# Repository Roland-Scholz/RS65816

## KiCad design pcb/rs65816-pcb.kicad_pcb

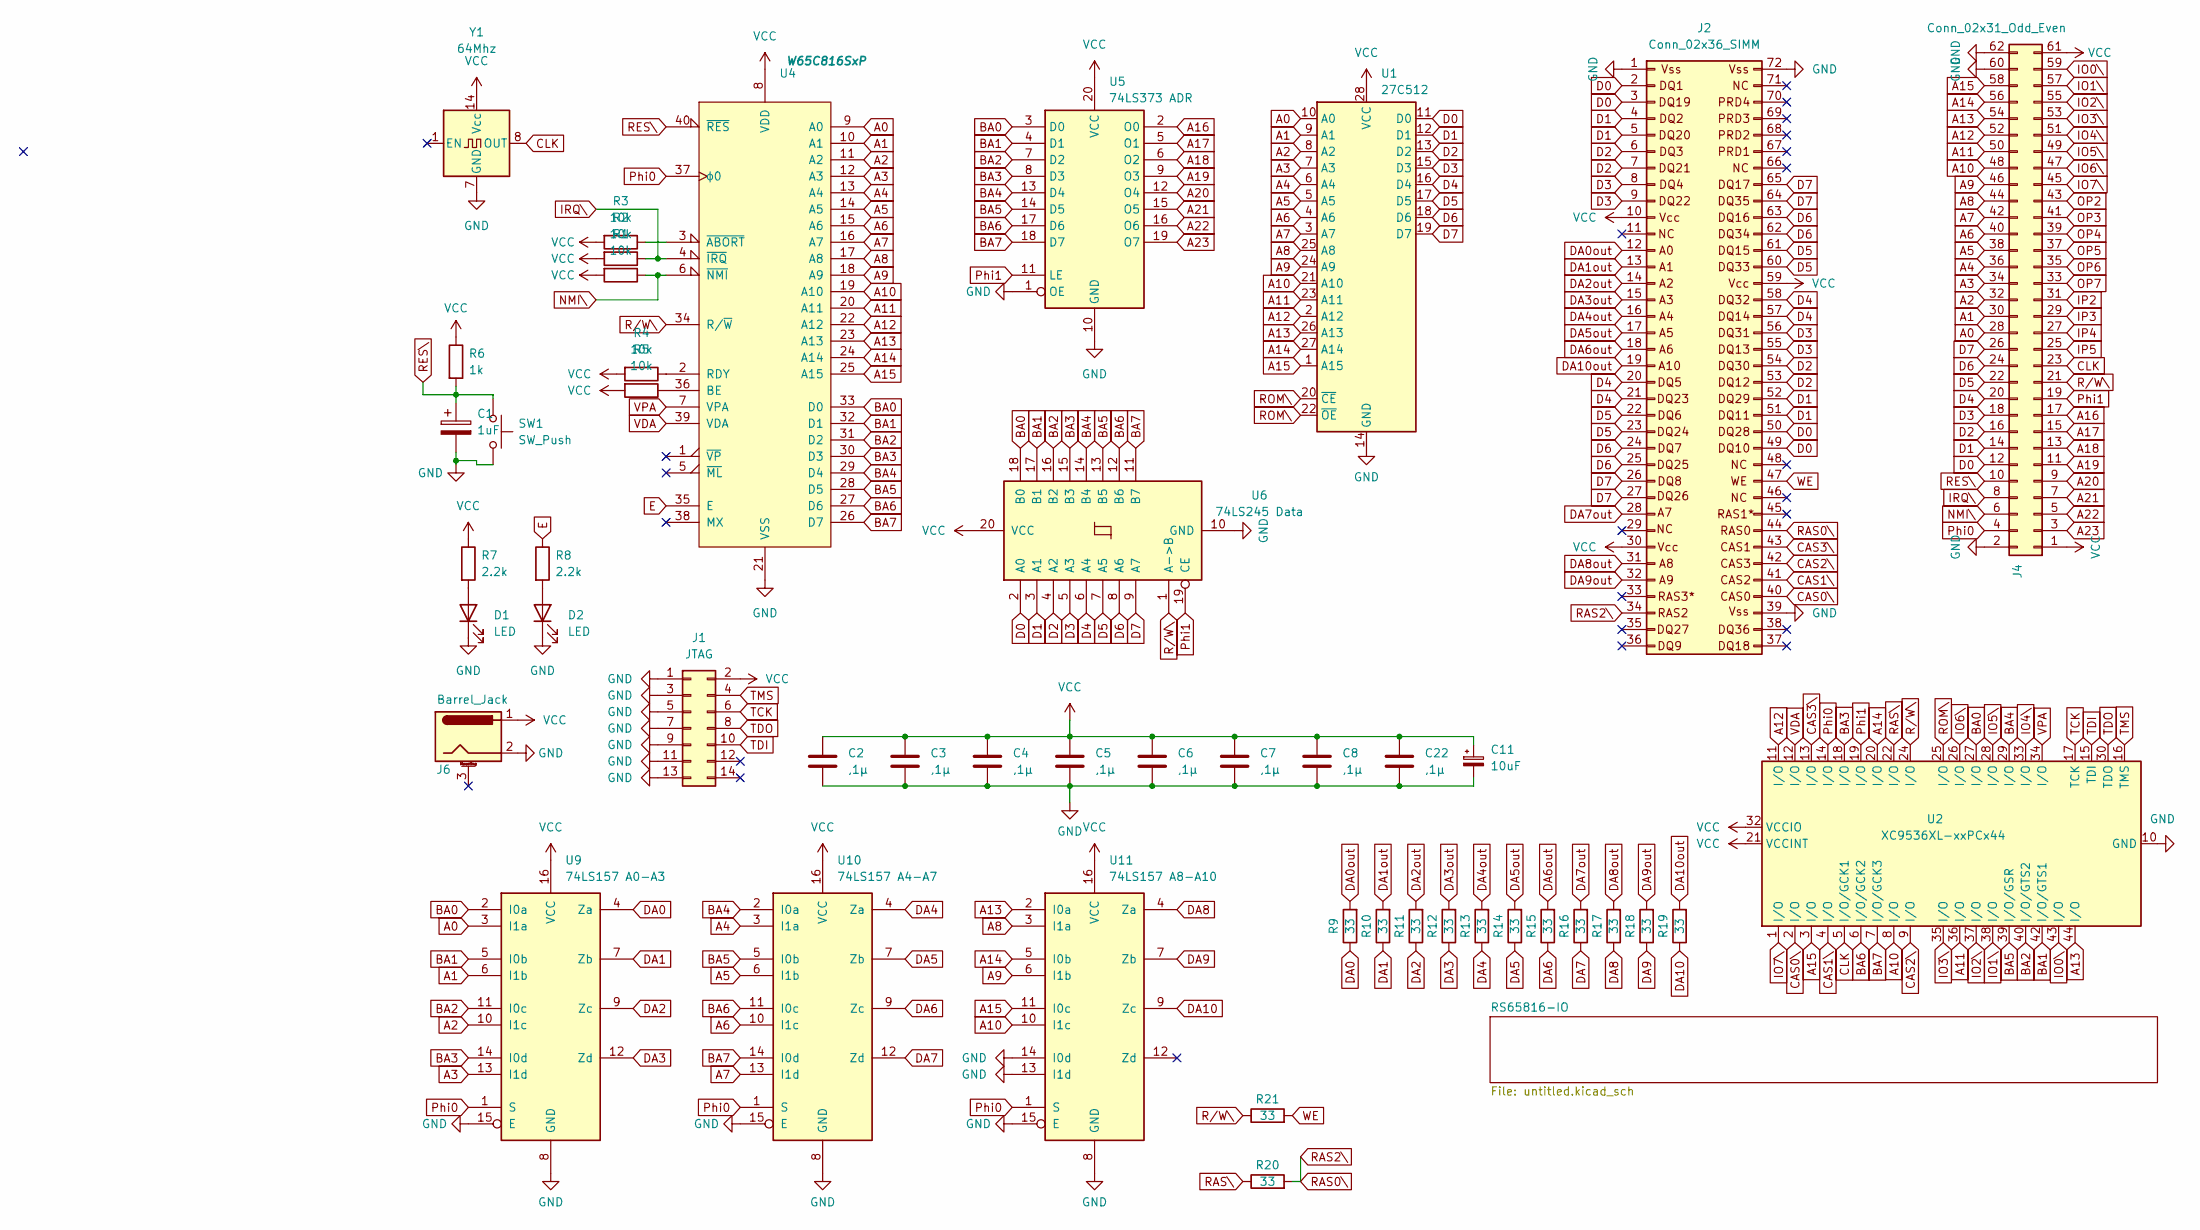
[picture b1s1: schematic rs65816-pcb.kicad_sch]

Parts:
C1: 1uF; CP_Radial_D5.0mm_P2.50mm
C2, C3, C4, C5, C6, C7, C8, C22: ,1µ; C_Disc_D5.0mm_W2.5mm_P5.00mm
C11: 10uF; CP_Radial_D5.0mm_P2.50mm
D1, D2: LED; LED_D5.0mm_Clear
J1: JTAG; PinHeader_2x07_P2.54mm_Vertical
J2: Conn_02x36_SIMM; SIM72
J4: Conn_02x31_Odd_Even; Conn_Edge_PCB_ISA8
J6: Barrel_Jack; BarrelJack_Horizontal
R1, R2, R3, R4, R5: 10k; R_Axial_DIN0207_L6.3mm_D2.5mm_P10.16mm_Horizontal
R6: 1k; R_Axial_DIN0207_L6.3mm_D2.5mm_P10.16mm_Horizontal
R7, R8: 2.2k; R_Axial_DIN0207_L6.3mm_D2.5mm_P10.16mm_Horizontal
R9, R10, R11, R12, R13, R14, R15, R16, R17, R18, R19, R20, R21: 33; R_Axial_DIN0207_L6.3mm_D2.5mm_P10.16mm_Horizontal
SW1: SW_Push; SW_PUSH_6mm
U1: 27C512; DIP-28_W15.24mm_Socket_LongPads
U2: XC9536XL-xxPCx44; PLCC-44_THT-Socket
U4: W65C816SxP; DIP-40_W15.24mm_Socket_LongPads
U5: 74LS373 ADR; DIP-20_W7.62mm_Socket_LongPads
U6: 74LS245 Data; DIP-20_W7.62mm_Socket_LongPads
U9: 74LS157 A0-A3; DIP-16_W7.62mm_Socket_LongPads
U10: 74LS157 A4-A7; DIP-16_W7.62mm_Socket_LongPads
U11: 74LS157 A8-A10; DIP-16_W7.62mm_Socket_LongPads
Y1: 64Mhz; Oscillator_DIP-14

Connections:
A0: J4.28, U1.10 (A0), U4.9 (A0), U9.3 (I1a); also elsewhere on the board
A1: J4.30, U1.9 (A1), U4.10 (A1), U9.6 (I1b); also elsewhere on the board
A2: J4.32, U1.8 (A2), U4.11 (A2), U9.10 (I1c); also elsewhere on the board
A3: J4.34, U1.7 (A3), U4.12 (A3), U9.13 (I1d); also elsewhere on the board
A4: J4.36, U1.6 (A4), U4.13 (A4), U10.3 (I1a)
A5: J4.38, U1.5 (A5), U4.14 (A5), U10.6 (I1b)
A6: J4.40, U1.4 (A6), U4.15 (A6), U10.10 (I1c)
A7: J4.42, U1.3 (A7), U4.16 (A7), U10.13 (I1d)
A8: J4.44, U1.25 (A8), U4.17 (A8), U11.3 (I1a)
A9: J4.46, U1.24 (A9), U4.18 (A9), U11.6 (I1b)
A10: J4.48, U1.21 (A10), U2.8 (I/O), U4.19 (A10), U11.10 (I1c)
A11: J4.50, U1.23 (A11), U2.36 (I/O), U4.20 (A11)
A12: J4.52, U1.2 (A12), U2.11 (I/O), U4.22 (A12)
A13: J4.54, U1.26 (A13), U2.44 (I/O), U4.23 (A13), U11.2 (I0a)
A14: J4.56, U1.27 (A14), U2.20 (I/O), U4.24 (A14), U11.5 (I0b)
A15: J4.58, U1.1 (A15), U2.3 (I/O), U4.25 (A15), U11.11 (I0c)
A16: J4.17, U5.2 (O0)
A17: J4.15, U5.5 (O1)
A18: J4.13, U5.6 (O2)
A19: J4.11, U5.9 (O3)
A20: J4.9, U5.12 (O4)
A21: J4.7, U5.15 (O5)
A22: J4.5, U5.16 (O6)
A23: J4.3, U5.19 (O7)
BA0: U2.27 (I/O), U4.33 (D0), U5.3 (D0), U6.18 (B0), U9.2 (I0a)
BA1: U2.42 (I/O/GTS1), U4.32 (D1), U5.4 (D1), U6.17 (B1), U9.5 (I0b)
BA2: U2.40 (I/O/GTS2), U4.31 (D2), U5.7 (D2), U6.16 (B2), U9.11 (I0c)
BA3: U2.18 (I/O), U4.30 (D3), U5.8 (D3), U6.15 (B3), U9.14 (I0d)
BA4: U2.29 (I/O), U4.29 (D4), U5.13 (D4), U6.14 (B4), U10.2 (I0a)
BA5: U2.39 (I/O/GSR), U4.28 (D5), U5.14 (D5), U6.13 (B5), U10.5 (I0b)
BA6: U2.6 (I/O/GCK2), U4.27 (D6), U5.17 (D6), U6.12 (B6), U10.11 (I0c)
BA7: U2.7 (I/O/GCK3), U4.26 (D7), U5.18 (D7), U6.11 (B7), U10.14 (I0d)
CAS0\: J2.40, U2.2 (I/O)
CAS1\: J2.41, U2.4 (I/O)
CAS2\: J2.42, U2.9 (I/O)
CAS3\: J2.43, U2.13 (I/O)
CLK: J4.23, U2.5 (I/O/GCK1), Y1.8 (OUT)
D0: J2.2, J2.3, J2.49, J2.50, J4.12, U1.11 (D0), U6.2 (A0); also elsewhere on the board
D1: J2.4, J2.5, J2.51, J2.52, J4.14, U1.12 (D1), U6.3 (A1); also elsewhere on the board
D2: J2.6, J2.7, J2.53, J2.54, J4.16, U1.13 (D2), U6.4 (A2); also elsewhere on the board
D3: J2.8, J2.9, J2.55, J2.56, J4.18, U1.15 (D3), U6.5 (A3); also elsewhere on the board
D4: J2.20, J2.21, J2.57, J2.58, J4.20, U1.16 (D4), U6.6 (A4); also elsewhere on the board
D5: J2.22, J2.23, J2.60, J2.61, J4.22, U1.17 (D5), U6.7 (A5); also elsewhere on the board
D6: J2.24, J2.25, J2.62, J2.63, J4.24, U1.18 (D6), U6.8 (A6); also elsewhere on the board
D7: J2.26, J2.27, J2.64, J2.65, J4.26, U1.19 (D7), U6.9 (A7); also elsewhere on the board
DA0: R9.1, U9.4 (Za)
DA0out: J2.12, R9.2
DA1: R10.1, U9.7 (Zb)
DA1out: J2.13, R10.2
DA2: R11.1, U9.9 (Zc)
DA2out: J2.14, R11.2
DA3: R12.1, U9.12 (Zd)
DA3out: J2.15, R12.2
DA4: R13.1, U10.4 (Za)
DA4out: J2.16, R13.2
DA5: R14.1, U10.7 (Zb)
DA5out: J2.17, R14.2
DA6: R15.1, U10.9 (Zc)
DA6out: J2.18, R15.2
DA7: R16.1, U10.12 (Zd)
DA7out: J2.28, R16.2
DA8: R17.1, U11.4 (Za)
DA8out: J2.31, R17.2
DA9: R18.1, U11.7 (Zb)
DA9out: J2.32, R18.2
DA10: R19.1, U11.9 (Zc)
DA10out: J2.19, R19.2
E: R8.1, U4.35 (E)
GND: C1.2, C2.2, C3.2, C4.2, C5.2, C6.2, C7.2, C8.2, C11.2, C22.2, D1.1 (K), D2.1 (K), J1.1, J1.3, J1.5, J1.7, J1.9, J1.11, J1.13, J2.1, J2.39, J2.72, J4.2, J4.60, J4.62, J6.2, SW1.2, U1.14 (GND), U2.10 (GND), U2.23 (GND), U2.31 (GND), U4.21 (VSS), U5.1 (OE), U5.10 (GND), U6.10 (GND), U9.8 (GND), U9.15 (E), U10.8 (GND), U10.15 (E), U11.8 (GND), U11.13 (I1d), U11.14 (I0d), U11.15 (E), Y1.7 (GND); also elsewhere on the board
IO0\: J4.59, U2.43 (I/O); also elsewhere on the board
IO1\: J4.57, U2.38 (I/O)
IO2\: J4.55, U2.37 (I/O)
IO3\: J4.53, U2.35 (I/O)
IO4\: J4.51, U2.33 (I/O)
IO5\: J4.49, U2.28 (I/O)
IO6\: J4.47, U2.26 (I/O)
IO7\: J4.45, U2.1 (I/O)
IP2: J4.31; also elsewhere on the board
IP3: J4.29; also elsewhere on the board
IP4: J4.27; also elsewhere on the board
IP5: J4.25; also elsewhere on the board
IRQ\: J4.8, R2.1, U4.4 (~IRQ); also elsewhere on the board
NMI\: J4.6, R1.1, U4.6 (~NMI)
unnamed: D1.2 (A), R7.2
unnamed: D2.2 (A), R8.2
unnamed: R5.1, U4.36 (BE)
unnamed: R4.1, U4.2 (RDY)
unnamed: R3.1, U4.3 (~ABORT)
OP2: J4.43; also elsewhere on the board
OP3: J4.41; also elsewhere on the board
OP4: J4.39; also elsewhere on the board
OP5: J4.37; also elsewhere on the board
OP6: J4.35; also elsewhere on the board
OP7: J4.33; also elsewhere on the board
Phi0: J4.4, U2.14 (I/O), U4.37 (ϕ0), U9.1 (S), U10.1 (S), U11.1 (S)
Phi1: J4.19, U2.19 (I/O), U5.11 (LE), U6.19 (CE)
RAS0\: J2.34, J2.44, R20.2
RAS\: R20.1, U2.22 (I/O)
RES\: C1.1, J4.10, R6.2, SW1.1, U4.40 (~RES); also elsewhere on the board
ROM\: U1.20 (~CE), U1.22 (~OE), U2.25 (I/O)
R/W\: J4.21, R21.1, U2.24 (I/O), U4.34 (R/~W), U6.1 (A->B); also elsewhere on the board
TCK: J1.6, U2.17 (TCK)
TDI: J1.10, U2.15 (TDI)
TDO: J1.8, U2.30 (TDO)
TMS: J1.4, U2.16 (TMS)
VCC: C2.1, C3.1, C4.1, C5.1, C6.1, C7.1, C8.1, C11.1, C22.1, J1.2, J2.10, J2.30, J2.59, J4.1, J4.61, J6.1, R1.2, R2.2, R3.2, R4.2, R5.2, R6.1, R7.1, U1.28 (VCC), U2.21 (VCCINT), U2.32 (VCCIO), U2.41 (VCCINT), U4.8 (VDD), U5.20 (VCC), U6.20 (VCC), U9.16 (VCC), U10.16 (VCC), U11.16 (VCC), Y1.14 (Vcc); also elsewhere on the board
VDA: U2.12 (I/O), U4.39 (VDA)
VPA: U2.34 (I/O), U4.7 (VPA)
WE: J2.47, R21.2

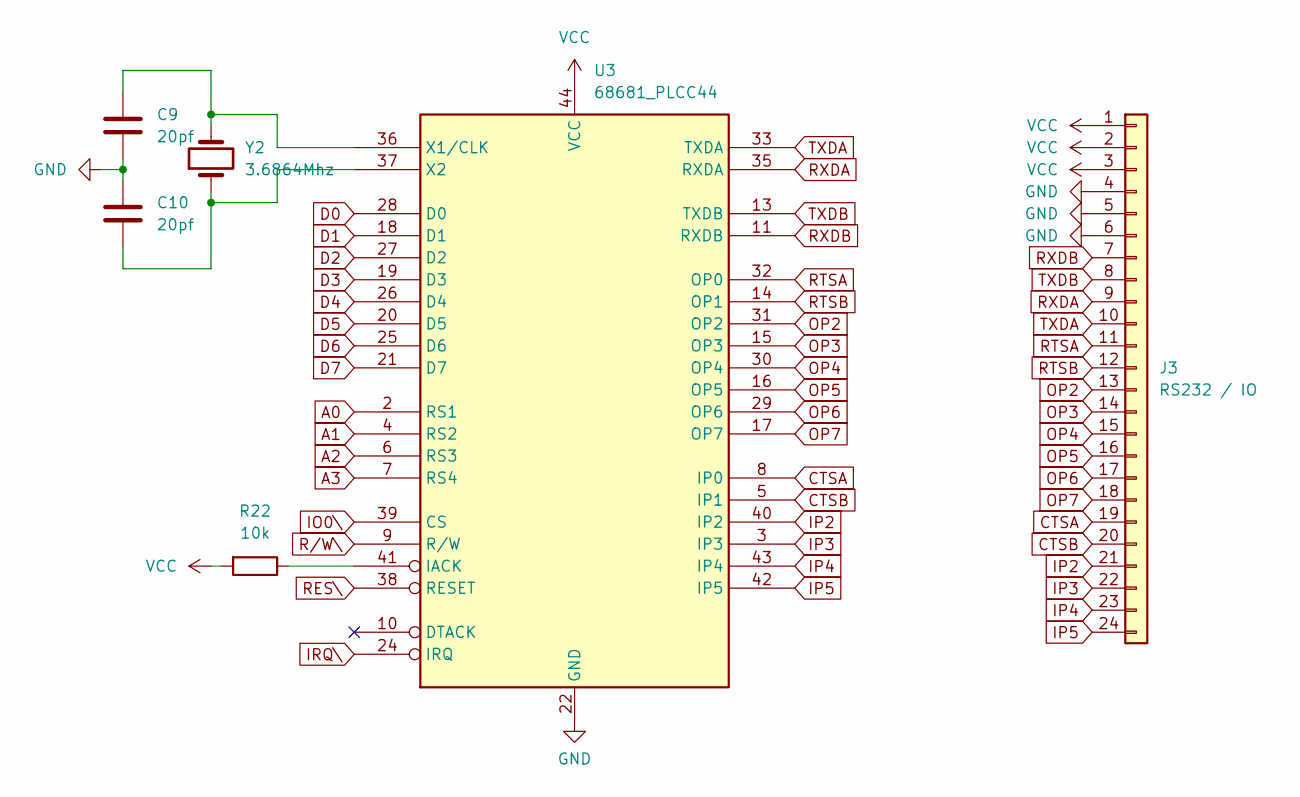
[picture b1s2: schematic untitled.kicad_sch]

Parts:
C9, C10: 20pf; C_Disc_D10.0mm_W2.5mm_P5.00mm
J3: RS232 / IO; PinHeader_1x24_P2.54mm_Vertical
R22: 10k; R_Axial_DIN0207_L6.3mm_D2.5mm_P10.16mm_Horizontal
U3: 68681_PLCC44
Y2: 3.6864Mhz; Crystal_HC49-U_Vertical

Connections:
A0: U3.2 (RS1); also elsewhere on the board
A1: U3.4 (RS2); also elsewhere on the board
A2: U3.6 (RS3); also elsewhere on the board
A3: U3.7 (RS4); also elsewhere on the board
CTSA: J3.19, U3.8 (IP0)
CTSB: J3.20, U3.5 (IP1)
D0: U3.28 (D0); also elsewhere on the board
D1: U3.18 (D1); also elsewhere on the board
D2: U3.27 (D2); also elsewhere on the board
D3: U3.19 (D3); also elsewhere on the board
D4: U3.26 (D4); also elsewhere on the board
D5: U3.20 (D5); also elsewhere on the board
D6: U3.25 (D6); also elsewhere on the board
D7: U3.21 (D7); also elsewhere on the board
GND: C9.2, C10.1, J3.4, J3.5, J3.6, U3.22 (GND); also elsewhere on the board
IO0\: U3.39 (CS); also elsewhere on the board
IP2: J3.21, U3.40 (IP2); also elsewhere on the board
IP3: J3.22, U3.3 (IP3); also elsewhere on the board
IP4: J3.23, U3.43 (IP4); also elsewhere on the board
IP5: J3.24, U3.42 (IP5); also elsewhere on the board
IRQ\: U3.24 (IRQ); also elsewhere on the board
unnamed: R22.1, U3.41 (IACK)
unnamed: C9.1, U3.36 (X1/CLK), Y2.2
unnamed: C10.2, U3.37 (X2), Y2.1
OP2: J3.13, U3.31 (OP2); also elsewhere on the board
OP3: J3.14, U3.15 (OP3); also elsewhere on the board
OP4: J3.15, U3.30 (OP4); also elsewhere on the board
OP5: J3.16, U3.16 (OP5); also elsewhere on the board
OP6: J3.17, U3.29 (OP6); also elsewhere on the board
OP7: J3.18, U3.17 (OP7); also elsewhere on the board
RES\: U3.38 (RESET); also elsewhere on the board
RTSA: J3.11, U3.32 (OP0)
RTSB: J3.12, U3.14 (OP1)
RXDA: J3.9, U3.35 (RXDA)
RXDB: J3.7, U3.11 (RXDB)
R/W\: U3.9 (R/W); also elsewhere on the board
TXDA: J3.10, U3.33 (TXDA)
TXDB: J3.8, U3.13 (TXDB)
VCC: J3.1, J3.2, J3.3, R22.2, U3.44 (VCC); also elsewhere on the board

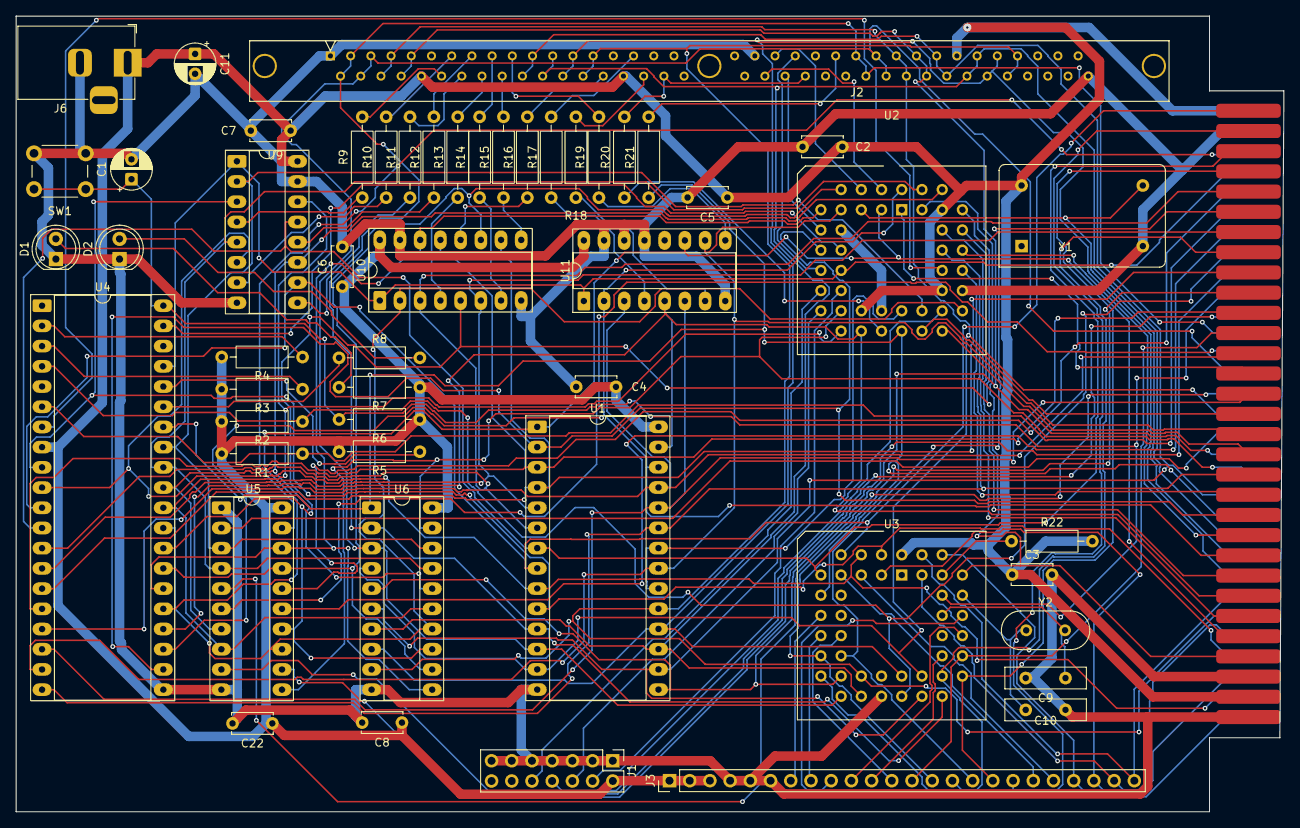
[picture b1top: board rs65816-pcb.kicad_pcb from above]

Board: 2 copper layers, 159.4 x 100.0 mm, 53 parts (0 on the bottom side), 120 nets.

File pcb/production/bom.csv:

Designator,Footprint,Quantity,Value,LCSC Part #
C1,CP_Radial_D5.0mm_P2.50mm,1,1uF,
"C10, C9",C_Disc_D10.0mm_W2.5mm_P5.00mm,2,20pf,
C11,CP_Radial_D5.0mm_P2.50mm,1,10uF,
"C2, C22, C3, C4, C5, C6, C7, C8",C_Disc_D5.0mm_W2.5mm_P5.00mm,8,",1µ",
"D1, D2",LED_D5.0mm_Clear,2,LED,
J1,PinHeader_2x07_P2.54mm_Vertical,1,JTAG,
J2,SIM72,1,Conn_02x36_SIMM,
J3,PinHeader_1x24_P2.54mm_Vertical,1,RS232 / IO,
J4,Conn_Edge_PCB_ISA8,1,Conn_02x31_Odd_Even,
J6,BarrelJack_Horizontal,1,Barrel_Jack,
"R1, R2, R22, R3, R4, R5",R_Axial_DIN0207_L6.3mm_D2.5mm_P10.16mm_Horizontal,6,10k,
"R10, R11, R12, R13, R14, R15, R16, R17, R18, R19, R20, R21, R9",R_Axial_DIN0207_L6.3mm_D2.5mm_P10.16mm_Horizontal,13,33,
R6,R_Axial_DIN0207_L6.3mm_D2.5mm_P10.16mm_Horizontal,1,1k,
"R7, R8",R_Axial_DIN0207_L6.3mm_D2.5mm_P10.16mm_Horizontal,2,2.2k,
SW1,SW_PUSH_6mm,1,SW_Push,
U1,DIP-28_W15.24mm_Socket_LongPads,1,27C512,
U10,DIP-16_W7.62mm_Socket_LongPads,1,74LS157 A4-A7,
U11,DIP-16_W7.62mm_Socket_LongPads,1,74LS157 A8-A10,
U2,PLCC-44_THT-Socket,1,XC9536XL-xxPCx44,
U3,PLCC-44_THT-Socket,1,68681_PLCC44,
U4,DIP-40_W15.24mm_Socket_LongPads,1,W65C816SxP,
U5,DIP-20_W7.62mm_Socket_LongPads,1,74LS373 ADR,
U6,DIP-20_W7.62mm_Socket_LongPads,1,74LS245 Data,
U9,DIP-16_W7.62mm_Socket_LongPads,1,74LS157 A0-A3,
Y1,Oscillator_DIP-14,1,64Mhz,
Y2,Crystal_HC49-U_Vertical,1,3.6864Mhz,

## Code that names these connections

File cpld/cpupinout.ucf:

NET io7      	LOC = FB2;
NET cas0     	LOC = P02;			
NET a15_13<2>	LOC = P03;
NET cas1     	LOC = P04;
NET clk      	LOC = P05;
NET bank<6>  	LOC = P06;
NET bank<7>  	LOC = P07;
NET a10      	LOC = P08;
NET cas2     	LOC = P09;
NET a12_11<1>	LOC = P11;
NET vda      	LOC = P12;
NET cas3     	LOC = P13;
NET phi0     	LOC = P14;
NET bank<3>  	LOC = P18;
NET phi1     	LOC = P19;
NET a15_13<1>	LOC = P20;
NET ras      	LOC = P22;

NET rw       	LOC = P24;
NET rom      	LOC = P25;
NET io6      	LOC = P26;
NET bank<0>  	LOC = P27;
NET io5      	LOC = P28;
NET bank<4>  	LOC = P29;
NET io4      	LOC = P33;
NET vpa      	LOC = P34;
NET io3      	LOC = P35;
NET a12_11<0>	LOC = P36;
NET io2      	LOC = P37;
NET io1      	LOC = P38;
NET bank<5>  	LOC = P39;
NET bank<2>  	LOC = P40;
NET bank<1>  	LOC = P42;
NET io0      	LOC = P43;
NET a15_13<0>	LOC = P44;
